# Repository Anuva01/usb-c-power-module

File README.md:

# ⚡ USB-C Power Module

A compact, open-source power delivery board that regulates USB-C input into clean, stable voltage rails while supporting Li-ion/LiPo battery charging and status indication. Designed in KiCad and fully DRC-clean, it's built to serve as a reliable power stage for embedded and portable electronics projects.

## Key Features

- 🔌 **USB-C Power Delivery** — Accepts standard USB-C input for power, eliminating the need for legacy micro-USB or barrel-jack connectors.
- 🔋 **Battery Charging & Connectivity** — Integrated charge management for single-cell Li-ion/LiPo batteries via the TP4056 charger IC, with a dedicated battery connector.
- 📟 **Regulated Voltage Rails** — Clean, stable 3.3V output using the AP2112K low-dropout (LDO) regulator, suitable for powering microcontrollers and sensitive analog/digital components.
- 💡 **Status Indicator LEDs** — Visual feedback for charging state (charging / fully charged) and power-good status at a glance.
- 🧰 **Filtered, Noise-Resistant Design** — Input/output capacitor filtering to smooth voltage ripple and suppress transient noise.
- ✅ **DRC-Clean Layout** — Passed KiCad's Design Rules Check with 0 errors and 0 warnings.

## Hardware Architecture

| Component | Purpose |
|---|---|
| **USB-C Receptacle** | Primary power input connector, supports standard USB-C cables |
| **TP4056** | Li-ion/LiPo battery charge management IC |
| **AP2112K** | Fixed 3.3V LDO voltage regulator for clean downstream power |
| **Input/Output Filter Capacitors** | Smooths voltage ripple and filters transient noise on both input and regulated output rails |
| **Indicator LEDs** | Visual status feedback for charging and power states |
| **Battery Connector (JST-PH or equivalent)** | Interface for connecting a single-cell Li-ion/LiPo battery |

## 📷 Visuals

## Getting Started

1. Clone this repository
2. Open `USB-C-Power-Module.kicad_pro` in KiCad (version 7.x or later recommended)
3. Review the schematic and PCB layout under the **Schematic Editor** and **PCB Editor**
4. Generate manufacturing files (Gerbers/BOM) via **File → Fabrication Outputs** if you plan to order the board

## Open Source & Contributions

This project is open source and contributions are welcome — whether it's design improvements, additional footprints, documentation fixes, or suggestions for alternative components.

- 🐛 Found an issue? Open a [GitHub Issue](../../issues)
- 🔧 Want to contribute? Fork the repo, make your changes, and submit a pull request
- 💬 Questions or ideas? Start a discussion or reach out directly

Please ensure any submitted changes pass KiCad's DRC with 0 errors before opening a PR.

## License

This project is licensed under the [CERN Open Hardware License](https://cern-ohl.web.cern.ch/) (or your preferred open hardware license) — see the LICENSE file for details.

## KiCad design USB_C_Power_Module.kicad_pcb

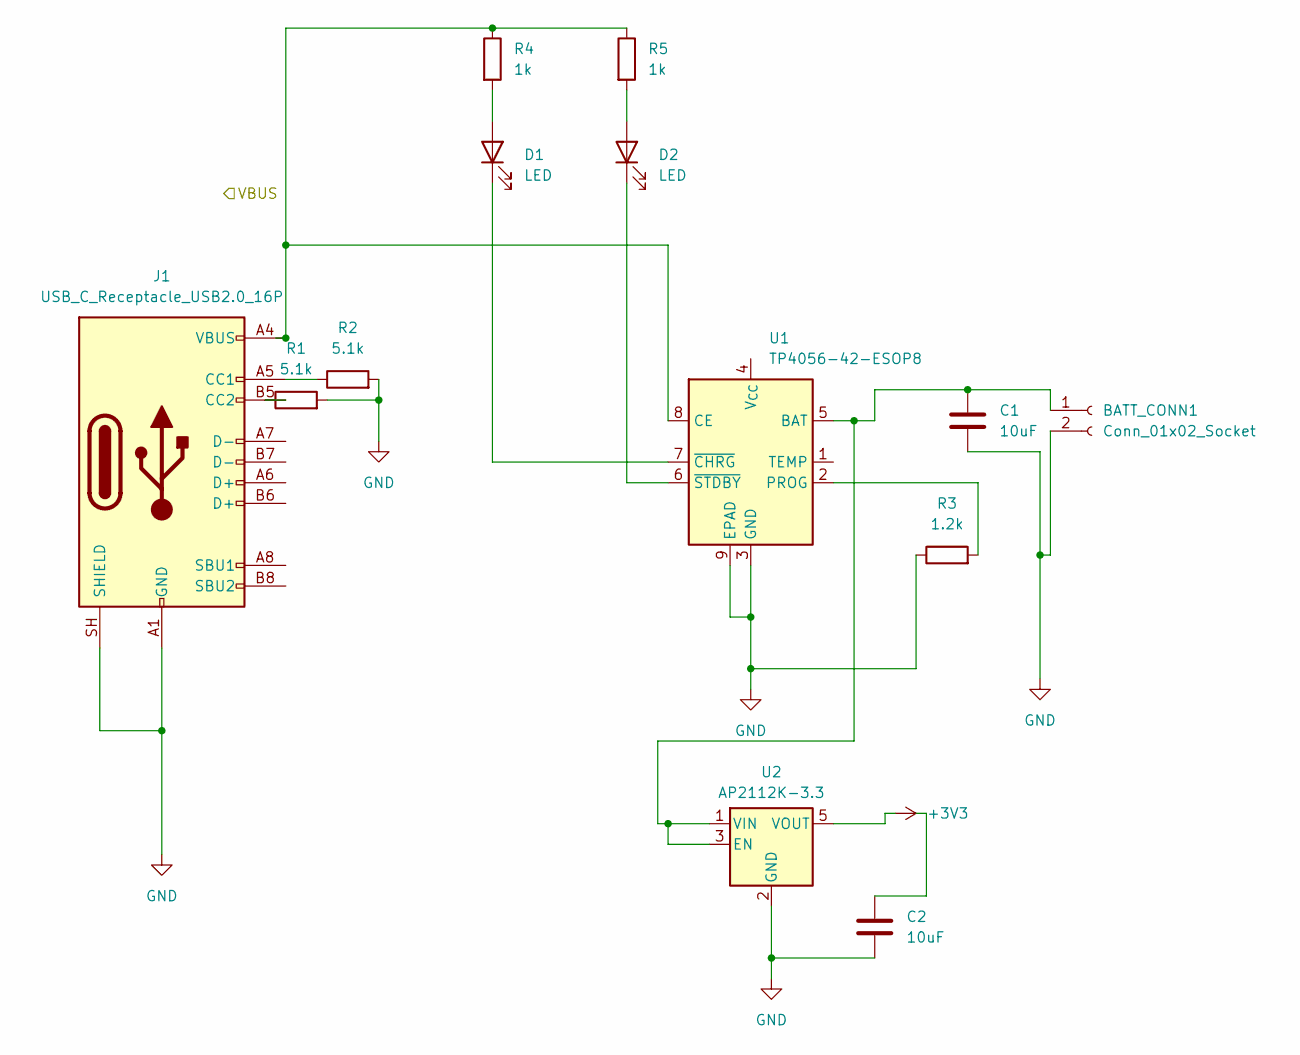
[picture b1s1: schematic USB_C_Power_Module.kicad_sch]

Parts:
BATT_CONN1: Conn_01x02_Socket; JST_PH_B2B-PH-K_1x02_P2.00mm_Vertical
C1, C2: 10uF; C_0805_2012Metric
D1, D2: LED; LED_0805_2012Metric
J1: USB_C_Receptacle_USB2.0_16P; USB_C_Receptacle_HRO_TYPE-C-31-M-12
R1, R2: 5.1k; R_0805_2012Metric
R3: 1.2k; R_0805_2012Metric
R4, R5: 1k; R_0805_2012Metric
U1: TP4056-42-ESOP8; SOIC-8-1EP_3.9x4.9mm_P1.27mm_EP2.29x3mm_ThermalVias
U2: AP2112K-3.3; SOT-23-5

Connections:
+3V3: U2.5 (VOUT)
GND: BATT_CONN1.2, C1.1, C2.2, J1.A1 (GND), J1.A12 (GND), J1.B1 (GND), J1.B12 (GND), J1.SH (SHIELD), R1.2, R2.2, R3.1, U1.3 (GND), U1.9 (EPAD), U2.2 (GND)
unnamed: BATT_CONN1.1, C1.2, U1.5 (BAT), U2.1 (VIN), U2.3 (EN)
unnamed: D1.2 (A), R4.2
unnamed: D1.1 (K), U1.7 (~CHRG)
unnamed: D2.2 (A), R5.2
unnamed: D2.1 (K), U1.6 (~STDBY)
unnamed: J1.A5 (CC1), R2.1
unnamed: J1.B5 (CC2), R1.1
unnamed: J1.A4 (VBUS), J1.A9 (VBUS), J1.B4 (VBUS), J1.B9 (VBUS), R4.1, R5.1, U1.8 (CE)
unnamed: R3.2, U1.2 (PROG)

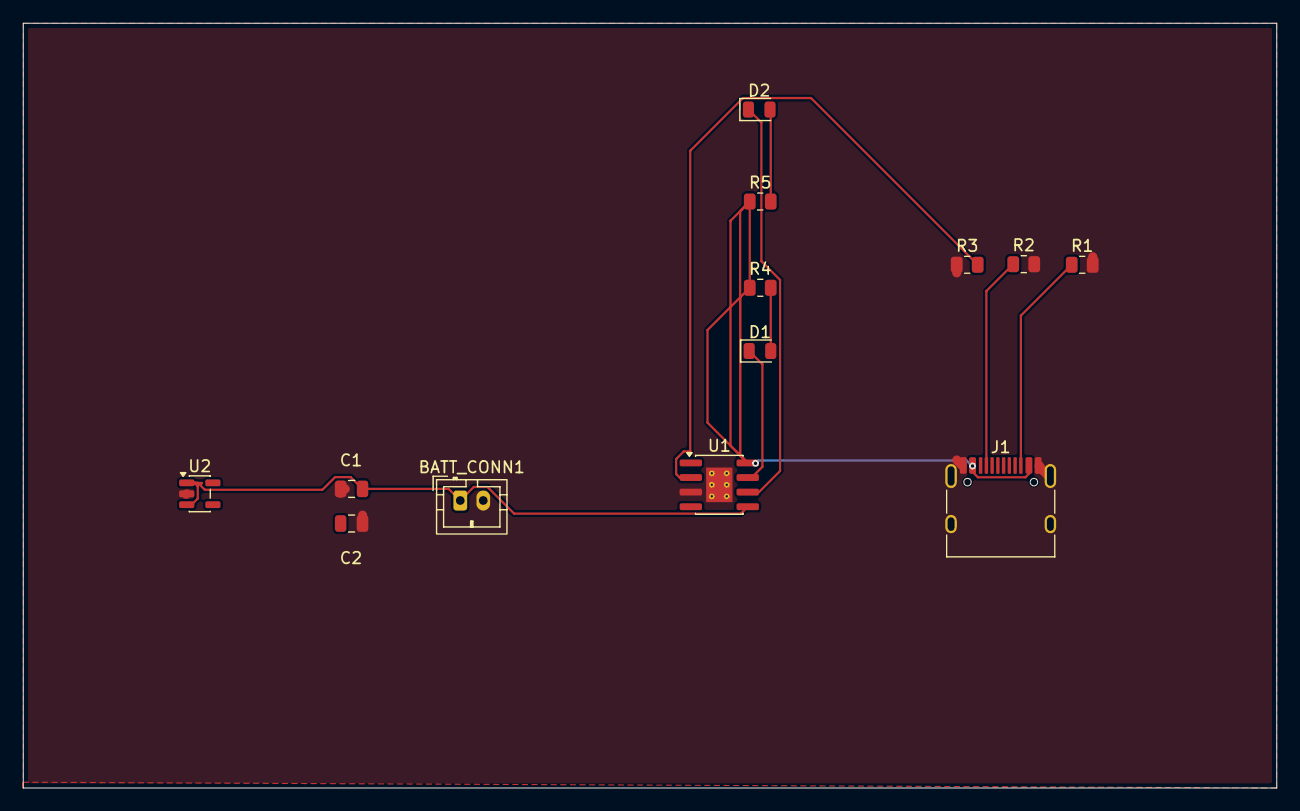
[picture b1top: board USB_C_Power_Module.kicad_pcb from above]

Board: 2 copper layers, 109.0 x 66.5 mm, 13 parts (0 on the bottom side), 10 nets.
